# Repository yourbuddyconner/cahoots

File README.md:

# Cahoots

Cahoots is a private network that only exists between people who have met in person. Meeting takes five minutes in a room: your devices make a shared secret that nobody outside the room has seen. After that you can message, log in and tunnel to each other with keys that no server ever had, and the keys rotate from that secret for years.

## The mental model

A one-time pad is a file of random bytes that a group of people share. To encrypt a message, you XOR it with fresh pad bytes. To decrypt, you XOR it with the same bytes. Each byte is used once and then destroyed. If the pad is truly random and never reused, no amount of computing power can break the encryption. That includes quantum computers.

The hard part is getting the same random file to every member without anyone else seeing it. Cahoots does this in person, at a **ceremony**:

1. A group meets in a room. Each person holds a Cahoots badge or a phone.
2. Each device generates random bytes from its hardware random number generator.
3. The devices swap those bytes over a wired touch link, or by showing each other animated codes. Each contribution is encrypted to the other members before it leaves the device, so a camera or an antenna in the room learns nothing.
4. Every device XORs all contributions into one shared pad.
5. Every device signs the list of seats with a key it made for this group, so the group has a signed roster and every member a key to sign with later.
6. The members read six check words aloud to confirm every device holds the same pad.

The group is now a **circle**. The pad is a key budget. Spending 32 bytes seeds a session of any size in WireGuard, HPKE, or age. An attacker then has to break both the math and the pad. Spending one byte per byte encrypts a short message that nothing can break. The device records every spend in a ledger and erases the bytes, so no key is ever used twice.

Ciphertext travels over the **Numbers Station**, an append-only public feed. Anyone can read it. Only circle members can decrypt or forge an entry.

A circle can also give a seat to a hosted software member, such as an AI agent. That member's copy of the pad lives inside a [Turnkey Verifiable Cloud (TVC)](https://docs.turnkey.com/features/verifiable-cloud/overview) enclave, and a pinned policy decides each read and send. This integration is optional. Circles without a hosted seat have a simple guarantee: nobody who runs the feed can read the circle.

## A badge with the chip

On a V1 board with the NXP SE051 secure element, the chip makes and holds each circle's seat key, and the key never leaves it. With it, a badge can:

- Show a proof from the chip that the seat key lives in it (attestation).
- Sign SSH logins, git commits and files. A laptop program asks, the badge shows the user and host, the commit's author and subject, or the file's first line and size, and it signs when both buttons are pressed.
- Sign a contact card and share its circle's card seal key, so a circle can swap cards.
- Sign grants as CBOR Web Tokens.
- Give an agent a grant to sign git commits on a budget, so each commit needs no press. The chip counts the uses.

A badge also keeps several circles at once, with nothing linking them, whether or not it has the chip: up to 16 on the Pico 2, and 4 on the Nano ESP32, which has no chip.

All of this is built and tested against a software chip, and on 2026-10-29 a Pico 2 with the SE051 did it on the bench: a ceremony with its seat key made in the chip, then a file and a git commit signed by the chip and verified by `ssh-keygen` and `git`. Attestation against NXP's root still waits. See [the roadmap](docs/plan.md) (M4f) and the [host program](crates/host/README.md).

## Repository layout

Every Rust crate lives under `crates/`. The PWA lives under `web/app`.

| Path | Crate | What it holds | Status |
|---|---|---|---|
| `crates/core` | `cahoots-core` | The protocol: parameters, commit-then-reveal ceremony, XOR combine, check words, circle ID, message codec with one-time Poly1305, spent-range ledger, spend ordering, touch-link framing. `no_std` + `alloc`. | done (M1) |
| `crates/vectors` | `cahoots-vectors` | JSON test vectors generated from core. Every client must reproduce them. | done (M1) |
| `crates/objects` | `cahoots-objects` | The four objects a seat signs, as canonical CBOR in COSE_Sign1: grants, approvals, facts and receipts, each verified against the circle's signed manifest, with a JSON projection and vectors. `no_std`. | done (M1c) |
| `crates/custodian` | `cahoots-custodian` | The `Custodian` trait (`psk`, `spend`, `remaining`), the CBOR request and response messages, and `serve`, which answers a request only when the device consents. The `Chip` family (attest, sign for SSH, sign a card or a grant, release a seal key) is in [protocol](docs/protocol.md) section 6; a laptop program and a badge must come from the same release. `no_std`. | done (M4e) |
| `crates/chip` | `cahoots-chip` | The `ChipOps` trait a badge's key store speaks, a software chip for tests, and the SE051 backend (feature `se05x`) the Pico 2 uses. `no_std`. | done in software (M4f); the chip on the bench is not |
| `crates/provider` | `cahoots-provider` | The memory and encrypted-file custodians, the HKDF session-key derivation, and the old `PadProvider` name for `Custodian`. | done (S1) |
| `crates/hpke` | `cahoots-hpke` | HPKE `mode_psk` adapter (X25519 and X-Wing suites). | done (S1) |
| `crates/age-plugin-cahoots` | `age-plugin-cahoots` | age plugin: recipient `cahoots:<circle>`. | done (S1), untested against the `age` CLI |
| `crates/wireguard` | `cahoots-wireguard` | WireGuard `PresharedKey` helper and the `cahoots-wg` CLI: announce, peers, issue, accept over the feed or by paste; `--apply` runs `wg set`. | done (S1, N1); `scripts/wg-demo.sh` runs a two-host tunnel in CI |
| `crates/relay` | `cahoots-relay` | Numbers Station client shared by the CLIs. | done |
| `crates/wasm` | `cahoots-wasm` | Browser bindings: ceremony, circle, fountain-coded animated QR, QR rendering. | done (M2) |
| `web/app` | | Offline PWA phone and laptop client, including hello words for calls. | done (M2), camera scanning untested |
| `crates/phone` | `cahoots-phone` | The iOS app's state machine behind UniFFI: ceremonies as animated codes, circles as CBOR records, chat through the relay with an outbox, hello words. Swift supplies the enclave signer and HTTP. `scripts/ios-framework.sh` builds the XCFramework. | in progress (the Rust side; the app is not built yet) |
| `crates/hal` | `cahoots-hal` | HAL traits, the ceremony driver over any set of touch links (a pile, a ring, a pair), pile discovery (seat and count from the stack), SP 800-90B health tests, persistent ledger. `no_std`. | done (M4a) |
| `crates/badge` | `cahoots-badge` | The badge crate: the `Board` trait and the badge program that runs on it. It boots, runs the ceremony, keeps the circle, and shows the words, a key as a code, or serves custodian requests. `no_std`. | done (M4e) |
| `crates/host` | `cahoots-host` | Desktop simulator: socket Link, file PadStore, PNG Display. Four processes, each with a socket to both neighbours, run a ceremony. | done (M4a) |
| `crates/esp32s3` | `cahoots-esp32s3` | `esp-hal` firmware for the Arduino Nano ESP32 with the 1.54" e-paper and two buttons: the four HAL traits on real hardware, the pile over USB with the laptop as the other cards. Built with the esp toolchain, outside the workspace. | in progress (M4b, first board) |
| `crates/rp2350` | `cahoots-rp2350` | `rp235x-hal` firmware for the Raspberry Pi Pico 2 on V1's pin map: the e-paper, two buttons, the chip's TRNG, the pad and ledger in flash through the boot ROM, USB to a laptop and two UARTs up and down a pile. | done on a breadboard Pico 2 (M4b, 2026-10-27): a ceremony with the laptop as the pile, the circle kept in flash |
| `crates/dabao` | | Xous app for the Baochip-1x Dabao, the V2 card. | placeholder (M4c, M5) |
| `crates/chat` | `cahoots-chat` | End-to-end chat keyed by the circle root: epoch keys, sender ratchets, ChaCha20-Poly1305, plus the `cahoots-chat` CLI demo. | done (C1, C3) |
| `crates/station` | `cahoots-station` | The Numbers Station relay: hash-chained log, reuse refusal, long-poll feed, display page, per-client rate limit, log cap, Dockerfile, and the [deploy recipe](deploy/relay/README.md) for the default relay. | done (C2, C7; `relay.cahoots.network` is up); the [TVC](https://docs.turnkey.com/features/verifiable-cloud/overview) deploy pending |
| `crates/fuzz` | | `cargo-fuzz` targets for every parser. Not a workspace member. | done |
| `docs/` | | Protocol spec, threat model, use cases, plan, ceremony guide. | |

## Build and test

```sh
cargo test --workspace
cargo clippy --workspace --all-targets -- -D warnings
cargo build -p cahoots-core --no-default-features --target thumbv7em-none-eabi   # no_std check
cargo build -p cahoots-core --target wasm32-unknown-unknown
cargo run -p cahoots-vectors -- --check     # committed vectors are current
```

The pinned toolchain is in `rust-toolchain.toml`. CI runs these commands, with `--all-features` on clippy and test, and also builds `cahoots-hal` and `cahoots-chat` for `thumbv7em-none-eabi`.

## Security limits

- Confidentiality is information-theoretic only for circles labelled `TRNG`, and only while no pad byte is reused. `CSPRNG` circles are computationally secure.
- The circle tag proves that some member wrote a message, not which member.
- A stolen device exposes that device's pad.
- Erasure on phone storage is best effort.
- Circles that seat an agent trust the enclave with their pad.

See `docs/threat-model.md` for the full list.

## What it is for

`docs/tiers.md` defines the device tiers, from a phone (T0) to inspected silicon (T4), and the rule that a circle is only as protected as its least protected member. `docs/use-cases.md` lists concrete uses: group chat, and bootstrapping WireGuard and mesh networks from a ceremony. `docs/gatherings.md` is the concept of a card for every gathering: storage, messages from old circles, the web of trust a card accumulates, and a social network with no accounts. `docs/attested-data.md` surveys what a network of attested sensor readings, signed by the badge's key store chip, could be used for. `docs/diy-badge.md` is how to build a badge, in any of the three hardware families. `docs/plan.md` is the roadmap. `docs/glossary.md` defines the terms.

## Working rules

Correctness of the crypto is the product. Every spend path erases before output. Every tag compare is constant time. The message decoder is property-tested against arbitrary bytes. The code uses standards where they exist: Poly1305 (RFC 8439), BIP-39 words, HPKE (RFC 9180), and HKDF (RFC 5869).

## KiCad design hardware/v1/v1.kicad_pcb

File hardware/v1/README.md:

# V1: the first badge you can order

A 54 × 86 mm two-layer board that a Raspberry Pi Pico 2 solders onto. Front: the raw 1.54" e-paper (Good Display GDEY0154D67) on its 24-pin flex, two tactile switches, the pin half of a magnetic pogo connector at the top end with its pins up through the lid, two JST-SH sockets and a Qwiic socket at the bottom edge, and a three-turn NFC loop around the board's edge. Back: the Pico 2 crosswise with its USB at the right edge, a CR2032 holder, a power switch, the panel's boost circuit, the NXP SE051 secure element with a switch that opens its antenna, a 10-pin expansion socket, four pockets for 5 × 2 mm magnets.

The plan it belongs to is [docs/manufacturing.md](../../docs/manufacturing.md). The hand-built version that comes first, a Pico 2 and the Waveshare module on a proto board, uses the same pin map; the table is at the bottom.

## Status

Drawn, checked and quoted (2026-10-27, with the secure element and the loop): five boards, through ProvenMetal at JLCPCB, about to be ordered and not yet received. The schematic passes KiCad's electrical check, the board passes its design rule check, the three agree on every net (`check.py`), and every part in `bom.csv` is in JLCPCB's stock under the code written next to it (checked 2026-10-27 through ProvenMetal). What has not happened: a person looking at the 3D view and a 1:1 printout, and the flex connector's contact side confirmed against the panel's flex. See the review list.

## Files

| File | What |
|---|---|
| `design.py` | The single source: every part, pad, net and position, the Pico pin map, the panel pinout. |
| `make_sch.py` | Draws `v1.kicad_sch` from it: each part with a labelled stub on every pin. Plain python3. |
| `make_pcb.py` | Builds `v1.kicad_pcb`: footprints placed from the table, outline, slot, pours, edge keep-outs. KiCad's Python. |
| `route.py` | Exports the board for Freerouting and imports the result, then fills the pours. KiCad's Python. |
| `check.py` | Schematic netlist versus `design.py` versus the board. KiCad's Python. |
| `make_bom.py` | `bom.csv` in the assembler's columns. |
| `make.sh`, `hero.sh` | The whole pipeline; the angled two-sided render. |
| `v1.kicad_pro`, `v1.kicad_sch`, `v1.kicad_pcb`, `bom.csv` | The generated project. Open `v1.kicad_pro` in KiCad to look. |
| `schematic.png`, `front.png`, `back.png`, `hero.png` | Renders of the schematic, both sides of the board, and an angled view of both for an article. |
| `models/panel.wrl` | A box model of the panel, so the 3D view shows the glass and the flex. |
| `case.py`, `case/` | The tray and lid: STEP, STL for the printer, transparent WRL for the render. |
| `explode.py`, `assembly.png` | The parts sheet: the badge exploded into lid, panel, board, cell, pins and tray beside the assembled badge, with a numbered list. |
| `parts.py`, `parts.png` | Each piece alone, front and back: lid, panel, board, tray. |
| `models/` | Models for the parts the libraries lack: panel, magnets, cell, the two pogo halves. |

Regenerate everything:

```sh
cd hardware/v1
PY=/Applications/KiCad.app/Contents/Frameworks/Python.framework/Versions/Current/bin/python3
python3 make_sch.py && python3 make_bom.py
$PY make_pcb.py && $PY route.py export
java -jar freerouting.jar -de v1.dsn -do v1.ses -mp 400 -da        # Freerouting 2.5 on Java 25; 2.1 never finished this board, and 2.5 needs the passes
$PY route.py import && $PY check.py
kicad-cli pcb drc --severity-error v1.kicad_pcb
kicad-cli pcb render --side top -o front.png v1.kicad_pcb
kicad-cli sch export svg -o out v1.kicad_sch          # schematic.png is a rendering of that SVG
```

Edit `design.py`, never the generated files: the next run overwrites them.

## What is on it

**Pico 2.** Soldered flat through its castellations, components facing out, USB overhanging the right edge, BOOTSEL reachable. Flashing is drag-and-drop over that USB. The library footprint is the Pico 1's; the Pico 2 has no castellated debug pads, so those three are dropped.

**Panel.** The flex leaves the panel's bottom edge 8.5 mm from its left corner and runs straight down into the connector on the front. The boost circuit is the panel specification's reference circuit, page 28: 47 µH, a MOSFET switched by the panel's own GDR pin, one Schottky up to VGH, a capacitor and two Schottkys pumping VGL negative, a 2.2 Ω sense resistor, and a 1 µF on each driven rail. BS1 to ground selects 4-wire SPI. The MOSFET is the AO3400A rather than the reference's Si1308EDL because it is a stocked basic part; its 30 V rating clears the panel's gate voltages.

**Rules.** Tracks are 0.25 mm with 0.2 mm clearance everywhere the router draws them. The board's minimums are JLCPCB's floor, 0.127 mm for both, which only the SE051's escape stubs use: its pads are on a 0.4 mm pitch, and each used pad gets a short locked stub at that width before the router takes over.

**Power.** CR2032 into a slide switch, through a Schottky into the Pico's VSYS. The Pico's buck-boost makes 3.3 V from anything above 1.8 V. The diode keeps USB power out of the cell. Whether a coin cell survives a ceremony is the open measurement in the manufacturing plan; the holder is the easy part to swap.

**Buttons.** A is next, B is confirm, each to ground on the chip's pull-ups.

**Secure element.** U2 on the back at the top right is the NXP SE051C2 in its 3 × 3 mm HX2QFN20, on I2C0 beside the Qwiic socket, with 3.3 kΩ pull-ups on the bus (a Qwiic board adds its own in parallel, which is fine at 3.3 V). Its ENA pin is on GP2 through a 100 kΩ pull-up: the chip is on until the firmware pulls the pin low for deep power-down. VOUT is tied to VCC on the board, as the data sheet asks when ENA is used, so the chip's own rail (SE_VCC) has its own 100 nF. RST_N is tied high; the ISO 7816 pins are left open; the centre pad is grounded.

**Antenna.** ANT1 is a rectangular spiral on the front around the whole board, just inside the magnet pockets: three turns of 0.4 mm copper on a 0.8 mm pitch, 52 × 71 mm outside, its two ends at the top-right corner over the chip. It is drawn as copper lines inside the ANT1 footprint, a net tie between its two pads, so the board's rules understand that one piece of copper joins the switch's net to the chip's. The SE051 resonates its antenna with 56 pF, which asks for about 2.5 µH at 13.56 MHz; the loop is about 1.4 µH in free space (`design.py` prints the estimate), and C15, 39 pF across LA and LB at the chip, brings it to 13.6 MHz, with C16's footprint (27 pF) left empty for trimming. The Pico, the cell and the back pour sit inside the loop and will pull the inductance down, so expect the first measurement to land high and need C16. SW4, the same slide switch as the power switch, is in the LA line between the chip and the loop: open, the loop is not a closed conductor and the chip sees only C15. The ground pours stay 1.2 mm clear of the turns on both layers, the front has no pour inside the loop, and no tracks or vias cross the turns on the front, which is why the three sockets at the bottom edge, the only parts outside the loop, each get a via of their own above their contacts. The firmware keeps the contactless interface disabled regardless of the switch; both off is the shipped state. (A loop around the panel alone was drawn first; its bottom edge ran along the Pico's lower pad row and the router could not get the top half of the board out.)

**Peripherals.** J5 at the bottom centre of the front is a Qwiic (STEMMA QT) socket, the same JST-SH 4-pin part as the pile ports, in the Qwiic pin order: 1 GND, 2 3V3, 3 SDA, 4 SCL, on the Pico's I2C0 (GP8 and GP9). Any Qwiic board plugs in with its own cable. J6 on the back, under the Qwiic socket at the bottom edge, is a 10-pin JST-SH socket, the same low side-entry family as the three front sockets: 3V3, GND and eight of the Pico's spare GPIO, for whatever a firmware fork needs to drive, on a cable out of the bottom end. Nothing else on the board uses those pins. (It was a 2x5 pin header until 2026-10-28; the badge is meant to stay low, and a header is 8 mm tall.)

**Pile links.** Badges stack face to face. J4 at the top end of the front is the pin half of an Adafruit 5413 magnetic connector (Weilichuang MG005): five pogo pins on 2.54 mm, a magnet at each end, 2 A rated, 0.9 mm stroke, standing on the board with its pins up through a window in the lid, 1.2 mm proud of the top. The pad half is not on the board: it sits face down in a window in the tray floor, flush with the outside, and a short JST-SH pigtail wires it to the DN socket J3 (its pin 1 to J3 pin 1, pin 2 to J3 pin 3, pin 4 to J3 pin 4). Stack two badges and the lower one's pins meet the upper one's pads, pin for pin, the magnets holding them; pins 1 and 5 are ground, 2 and 4 the UART, 3 spare. Pin 3 carries no power: feeding one badge's regulator from another's is a question for V2, and two UART lines and ground are the pile. J2 and J3 are JST-SH 4-pin sockets at the bottom edge, UP and DN, for a cable to a badge on the bench or a laptop; a straight cable works because TX and RX are crossed between the two. There is no detect wire: a connected peer's TX holds our RX high, and the firmware keeps a pull-down on each RX. UP is UART0, DN is UART1.

## Pin map

| Signal | Pico 2 GPIO | Pico pin | Hand build: Waveshare module / part |
|---|---|---|---|
| EPD_SCK | GP18 | 24 | CLK |
| EPD_MOSI | GP19 | 25 | DIN |
| EPD_CS | GP17 | 22 | CS |
| EPD_DC | GP16 | 21 | DC |
| EPD_RST | GP20 | 26 | RST |
| EPD_BUSY | GP21 | 27 | BUSY |
| BTN_A | GP14 | 19 | switch A to GND |
| BTN_B | GP15 | 20 | switch B to GND |
| I2C_SDA | GP8 | 11 | J5 pin 3 (Qwiic SDA), U2 pin 9 |
| I2C_SCL | GP9 | 12 | J5 pin 4 (Qwiic SCL), U2 pin 10 |
| SE_ENA | GP2 | 4 | U2 pin 11; low is deep power-down, 100 kΩ pull-up |
| GP6, GP7 | GP6, GP7 | 9, 10 | J6 pins 3, 4 (J6 pin 1 is 3V3, pin 2 GND) |
| GP10, GP11, GP12, GP13 | GP10 to GP13 | 14, 15, 16, 17 | J6 pins 5, 6, 7, 8 |
| GP22, GP26 | GP22, GP26 | 29, 31 | J6 pins 9, 10 |
| UP_TX | GP0 | 1 | J4 pin 2, J2 pin 3 |
| UP_RX | GP1 | 2 | J4 pin 4, J2 pin 4; pull-down, high means a peer |
| DN_RX | GP5 | 7 | J3 pin 3, and through the pigtail the floor pad 2; pull-down, high means a peer |
| DN_TX | GP4 | 6 | J3 pin 4, floor pad 4 |
| 3V3 | 3V3 | 36 | module VCC |
| GND | GND | 3, 8, 13, 18, 23, 28, 38 | module GND, switches, pogo pins 1 and 5, both sockets' pin 1 |
| VSYS | VSYS | 39 | CR2032 + through the switch and a Schottky |

The Pico 2 firmware must use this table. For the hand build the Waveshare module replaces the panel, the connector and the whole boost circuit, since it carries them on its own board.

## The case

Two printed parts that click together, drawn by `case.py` from the same table (`CASE` in `design.py`), in `case/`: `tray.step`/`.stl` and `lid.step`/`.stl`, plus `.wrl` copies KiCad shows in the 3D view, transparent like the acrylic version will be.

- **Tray.** The board drops in face up onto a ledge. The floor sits 5.6 mm under the board, past the Pico and the cell in its holder, with a notch for the USB socket, three openings in the end wall for the cables (the middle one continues below the board for the expansion socket on the back), two openings in the floor under the slide switches, the pad half's window, four magnet pockets.
- **Lid.** A 2 mm plate on a 4 mm skirt that wraps outside the tray's wall. The panel is taped to the board, not to the lid, so the board comes out of the case as one unit with its screen (decided 2026-10-28; the first drawing glued the panel into the lid for a flush top). The plate's window shows the active area with a 1.5 mm lip over the panel's edge, and a frame under the lip comes down to 0.15 mm above the glass so the panel cannot lift, with a gap where the flex leaves; the glass sits about 3 mm below the lid's top. Two 7 mm holes over the switch stems, the pogo window, three socket windows, four magnet pockets, and the cable openings continued through its skirt, which reaches down past the board to the snaps. Four ribs press the board onto the tray's ledge.
- **The click.** Four wedge bumps on the inside of the skirt, on short slit tabs so they flex, drop into four windows through the tray's wall. PETG flexes better than PLA for this; if a tab cracks, make `snap` smaller or `skirt_t` thinner in the table. Screws are the fallback and need no redesign: the corner pockets become holes.
- **Printing.** Tray floor down, lid plate down, no supports needed except the USB notch bridge. Clear PETG shows the board; resin or cut acrylic later from the same STEP.
- **Sizes.** Tray 57.8 × 89.8 mm; the badge in its case 60.4 × 92.4 × 15 mm.

The lid's cavity is 2.2 mm high, enough for the flex connector and the taped panel (1.15); the pogo body (4.0) and the socket bodies (4.3) rise into windows in the 2 mm plate, and the pad half sits in a matching window in the floor. The badge is 13.4 mm thick.

Regenerate: `python3 case.py` with CadQuery installed (`python3 -m venv cq && cq/bin/pip install cadquery && cq/bin/python case.py`), then `make.sh` picks the models up.

## Review before ordering

1. **Flex connector contact side.** The footprint is a bottom-contact, flip-lock 0.5 mm connector. The panel's flex must present its contacts on the matching side when it runs straight down from the panel. If the flex's contacts face the other way, swap to a top-contact part of the same footprint family, or fold the flex. This is the classic mistake with e-paper; check it against a real panel in hand.
2. **Connector orientation.** Pin 1 of the connector must meet pin 1 of the flex, which is the panel's left pin in its drawing. Confirm in the 3D view with the flex overlaid.
3. **Part numbers.** Done 2026-10-27: every line in `bom.csv` resolves to a part in JLCPCB's stock (the 2.2 Ω sense resistor had the code of a 22 Ω part; fixed). The Pico 2 and the pogo pins are marked not fitted and soldered by hand; so is C16, the antenna trim.
4. **Battery holder footprint.** Drawn as MYOUNG BS-07; if the stocked holder is another family, the footprint changes.
5. **Pogo pair.** The footprint is drawn from the Weilichuang drawing, not a library part: check the 1.0 mm drills on 2.54 mm and the 4.0 mm body height against a real one before ordering boards. Print a tray and lid and stack two: the pins should land on the pads with the magnets pulling.
6. **Thickness and the tray.** Panel 1 mm plus the connector's 2 mm on the front; Pico 1 mm plus its parts and the holder on the back. The tray design is not here yet.
7. **Look at it.** Open `v1.kicad_pro`, press Alt-3 for the 3D view, and print the front at 1:1.
8. **The antenna.** When boards arrive: with SW4 closed and the chip's contactless interface enabled, read the chip with an NFC reader and note the distance. If it reads only when touching or not at all, measure the loop's resonance (a nanoVNA across LA and LB with the chip out of circuit, or by sweeping the reader) and fit C16 to pull it to 13.56 MHz. The loop geometry and the two capacitor footprints are in `design.py`; the exposed-pad size of the QFN-20 footprint is KiCad's generic 1.65 mm, not NXP's drawing, which only matters for the solder joint of a pad that is electrically unused.
9. **The switches.** SW1 and SW4 are on the back, facing the tray floor, which has a 9 × 5 mm opening under each (`switch_win` in the case table) for a fingernail. Check the openings land on the actuators with a printed tray before gluing anything.

## Not in V1

Flash encryption in firmware, the dock, the thin cell, the final tray. Those are V2's questions once the power measurement is in.

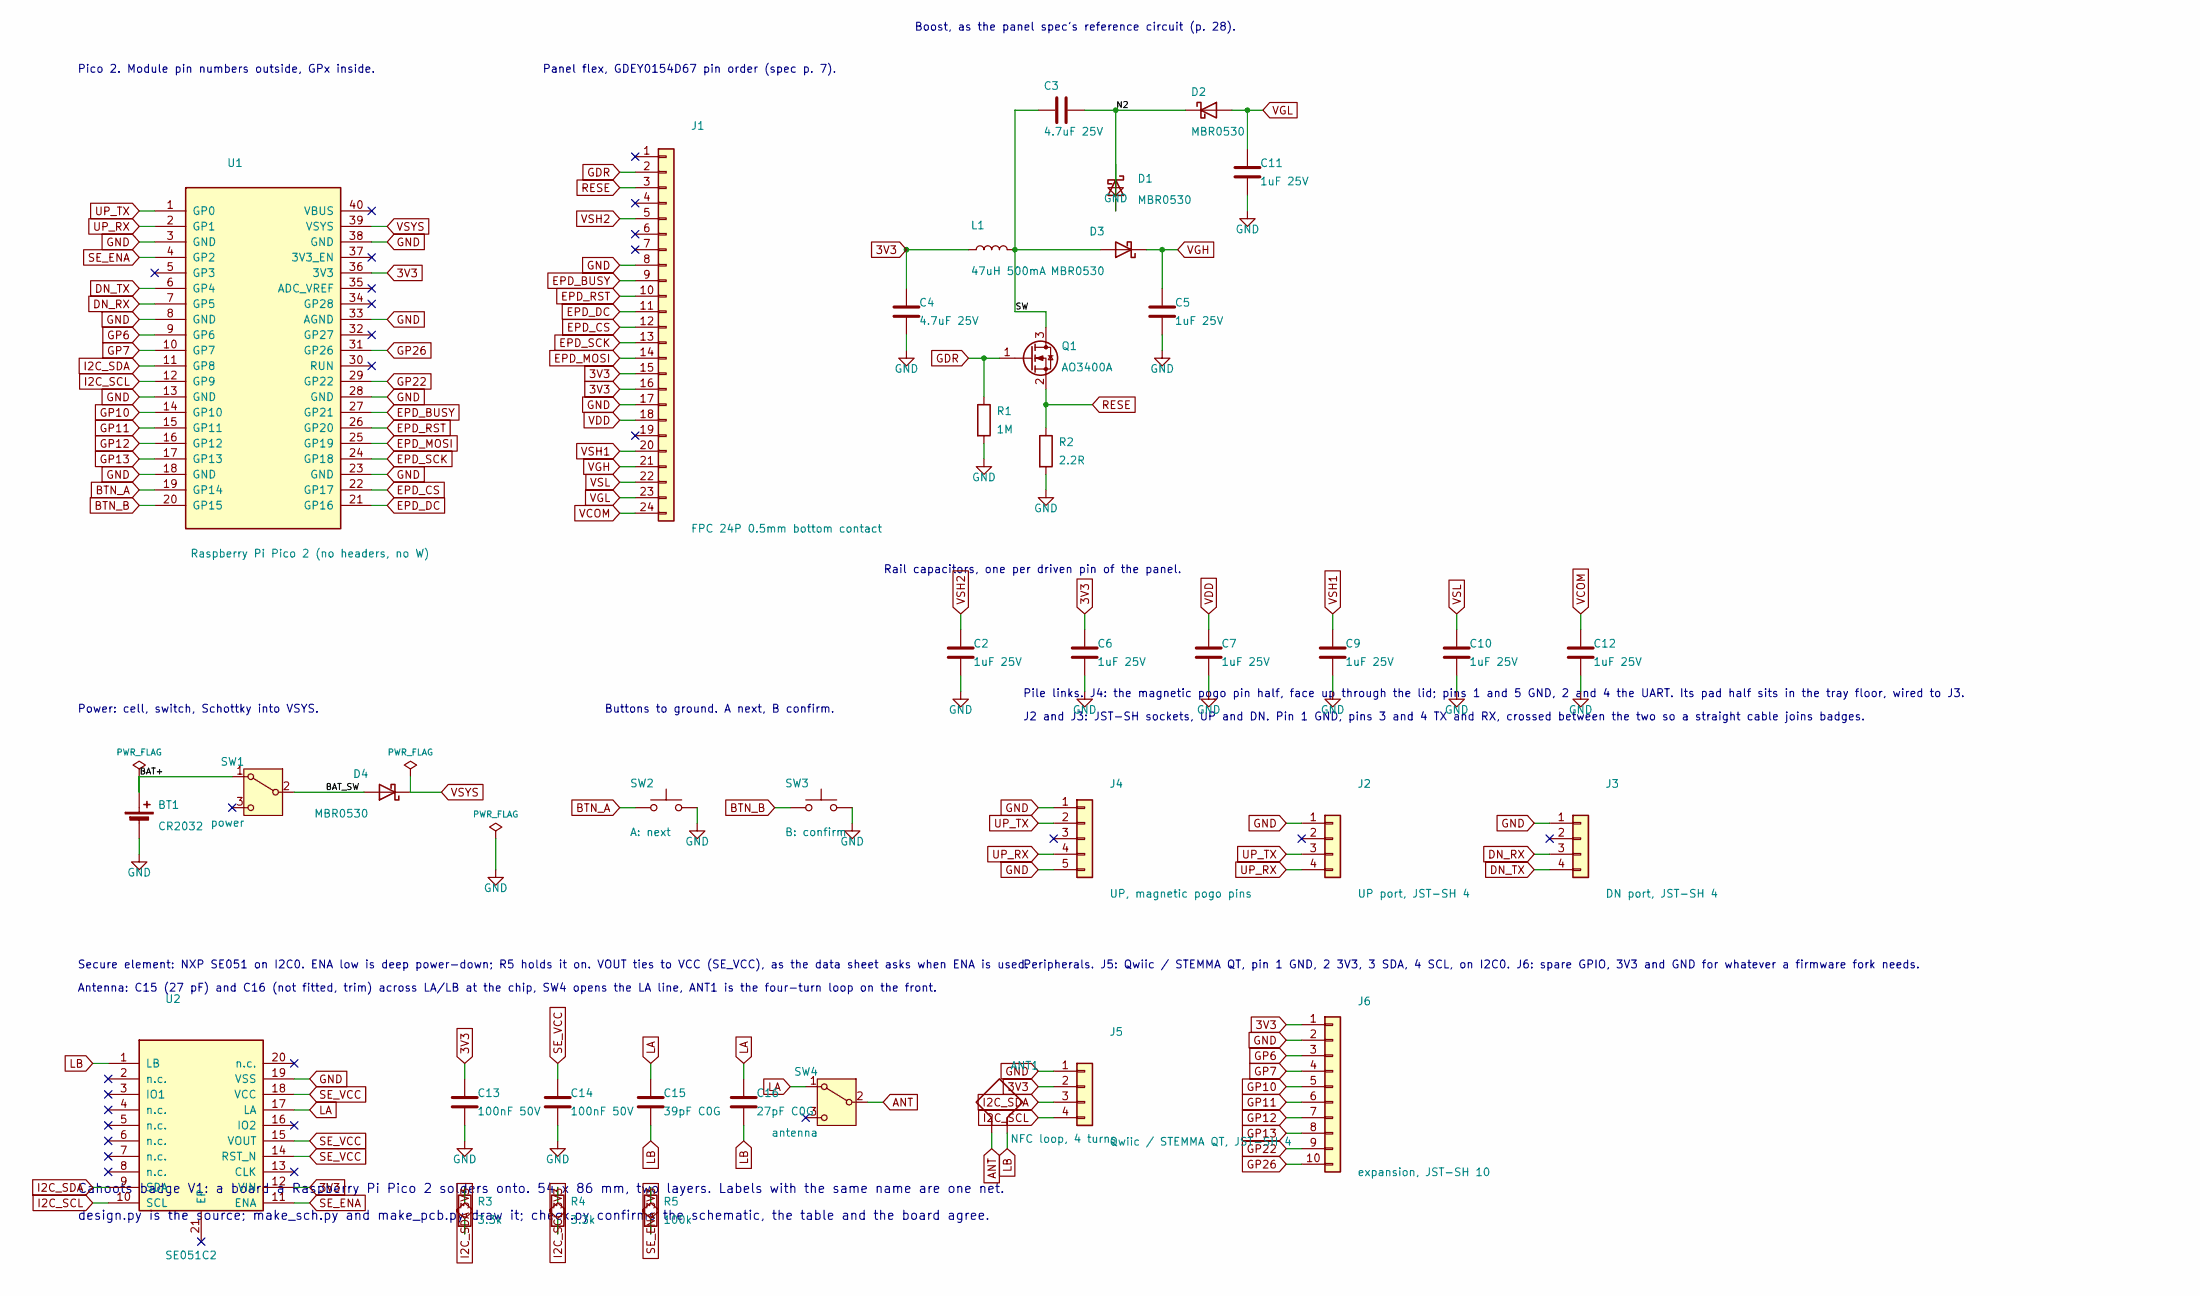
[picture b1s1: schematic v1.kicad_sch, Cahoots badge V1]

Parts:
ANT1: NFC loop, 4 turns; NFC_loop; LCSC board copper
BT1: CR2032; BatteryHolder_MYOUNG_BS-07-A1BJ001_CR2032; LCSC C2979167 MYOUNG BS-07-A1BJ001
C2, C5, C6, C7, C9, C10, C11, C12: 1uF 25V; C_0603_1608Metric; LCSC C15849
C3, C4: 4.7uF 25V; C_0805_2012Metric; LCSC C1779
C13, C14: 100nF 50V; C_0603_1608Metric; LCSC C14663
C15: 39pF C0G; C_0603_1608Metric; LCSC C107049 CC0603JRNPO9BN390, 39 pF
C16: 27pF C0G; C_0603_1608Metric; LCSC C107045 not fitted: antenna trim
D1, D2, D3, D4: MBR0530; D_SOD-123; LCSC C77336
J1: FPC 24P 0.5mm bottom contact; Hirose_FH12-24S-0.5SH_1x24-1MP_P0.50mm_Horizontal; LCSC C2856805 XUNPU FPC-05F-24PH20 (verify c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
J2: UP port, JST-SH 4; JST_SH_SM04B-SRSS-TB_1x04-1MP_P1.00mm_Horizontal; LCSC C160404 JST SM04B-SRSS-TB
J3: DN port, JST-SH 4; JST_SH_SM04B-SRSS-TB_1x04-1MP_P1.00mm_Horizontal; LCSC C160404 JST SM04B-SRSS-TB
J4: UP, magnetic pogo pins; Pogo_MG005_1x05; LCSC Adafruit 5413 pair, pin half
J5: Qwiic / STEMMA QT, JST-SH 4; JST_SH_SM04B-SRSS-TB_1x04-1MP_P1.00mm_Horizontal; LCSC C160404 JST SM04B-SRSS-TB
J6: expansion, JST-SH 10; JST_SH_SM10B-SRSS-TB_1x10-1MP_P1.00mm_Horizontal; LCSC C160409 JST SM10B-SRSS-TB
L1: 47uH 500mA; L_Changjiang_FNR4030S; LCSC C167888 FNR4030S470MT
Q1: AO3400A; SOT-23; LCSC C20917 (Si1308EDL in the reference; 30 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
R1: 1M; R_0603_1608Metric; LCSC C22935
R2: 2.2R; R_0603_1608Metric; LCSC C22939 0603WAF220KT5E, 2.2 ohm
R3, R4: 3.3k; R_0603_1608Metric; LCSC C22978
R5: 100k; R_0603_1608Metric; LCSC C25803
SW1: power; SW_SPDT_Shouhan_MSK12C02; LCSC C431540 MSK-12C02
SW2: A: next; SW_Push_1P1T_XKB_TS-1187A; LCSC C318884 TS-1187A-B-A-B
SW3: B: confirm; SW_Push_1P1T_XKB_TS-1187A; LCSC C318884 TS-1187A-B-A-B
SW4: antenna; SW_SPDT_Shouhan_MSK12C02; LCSC C431540 MSK-12C02
U1: Raspberry Pi Pico 2 (no headers, no W); RaspberryPi_Pico_SMD; LCSC not fitted: solder by hand
U2: SE051C2; QFN-20-1EP_3x3mm_P0.4mm_EP1.65x1.65mm; LCSC C5202100 NXP SE051C2HQ1/Z01XDZ

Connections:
3V3: C4.1, C6.1, C13.1, J1.15, J1.16, J5.2, J6.1, L1.1, R3.2, R4.2, R5.2, U1.36 (3V3), U2.12 (VIN)
ANT: ANT1.1, SW4.2 (B)
BAT+: BT1.1 (+), SW1.1 (A)
BAT_SW: D4.2 (A), SW1.2 (B)
BTN_A: SW2.1, U1.19 (GP14)
BTN_B: SW3.1, U1.20 (GP15)
DN_RX: J3.3, U1.7 (GP5)
DN_TX: J3.4, U1.6 (GP4)
EPD_BUSY: J1.9, U1.27 (GP21)
EPD_CS: J1.12, U1.22 (GP17)
EPD_DC: J1.11, U1.21 (GP16)
EPD_MOSI: J1.14, U1.25 (GP19)
EPD_RST: J1.10, U1.26 (GP20)
EPD_SCK: J1.13, U1.24 (GP18)
GDR: J1.2, Q1.1 (G), R1.1
GP6: J6.3, U1.9 (GP6)
GP7: J6.4, U1.10 (GP7)
GP10: J6.5, U1.14 (GP10)
GP11: J6.6, U1.15 (GP11)
GP12: J6.7, U1.16 (GP12)
GP13: J6.8, U1.17 (GP13)
GP22: J6.9, U1.29 (GP22)
GP26: J6.10, U1.31 (GP26)
I2C_SCL: J5.4, R4.1, U1.12 (GP9), U2.10 (SCL)
I2C_SDA: J5.3, R3.1, U1.11 (GP8), U2.9 (SDA)
LA: C15.1, C16.1, SW4.1 (A), U2.17 (LA)
LB: ANT1.2, C15.2, C16.2, U2.1 (LB)
RESE: J1.3, Q1.2 (S), R2.1
SE_ENA: R5.1, U1.4 (GP2), U2.11 (ENA)
SE_VCC: C14.1, U2.14 (RST_N), U2.15 (VOUT), U2.18 (VCC)
SW: C3.1, D3.2 (A), L1.2, Q1.3 (D)
UP_RX: J2.4, J4.4, U1.2 (GP1)
UP_TX: J2.3, J4.2, U1.1 (GP0)
VCOM: C12.1, J1.24
VDD: C7.1, J1.18
VGH: C5.1, D3.1 (K), J1.21
VGL: C11.1, D2.2 (A), J1.23
VSH1: C9.1, J1.20
VSH2: C2.1, J1.5
VSL: C10.1, J1.22
VSYS: D4.1 (K), U1.39 (VSYS)

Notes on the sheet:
Pico 2. Module pin numbers outside, GPx inside.
Panel flex, GDEY0154D67 pin order (spec p. 7).
Boost, as the panel spec's reference circuit (p. 28).
Rail capacitors, one per driven pin of the panel.
Power: cell, switch, Schottky into VSYS.
Buttons to ground. A next, B confirm.
Pile links. J4: the magnetic pogo pin half, face up through the lid; pins 1 and 5 GND, 2 and 4 the UART. Its pad half sits in the tray floor, wired to J3.
J2 and J3: JST-SH sockets, UP and DN. Pin 1 GND, pins 3 and 4 TX and RX, crossed between the two so a straight cable joins badges.
Peripherals. J5: Qwiic / STEMMA QT, pin 1 GND, 2 3V3, 3 SDA, 4 SCL, on I2C0. J6: spare GPIO, 3V3 and GND for whatever a firmware fork needs.
Secure element: NXP SE051 on I2C0. ENA low is deep power-down; R5 holds it on. VOUT ties to VCC (SE_VCC), as the data sheet asks when ENA is used.
Antenna: C15 (27 pF) and C16 (not fitted, trim) across LA/LB at the chip, SW4 opens the LA line, ANT1 is the four-turn loop on the front.
Cahoots badge V1: a board a Raspberry Pi Pico 2 solders onto. 54 x 86 mm, two layers. Labels with the same name are one net.
design.py is the source; make_sch.py and make_pcb.py draw it; check.py confirms the schematic, the table and the board agree.

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
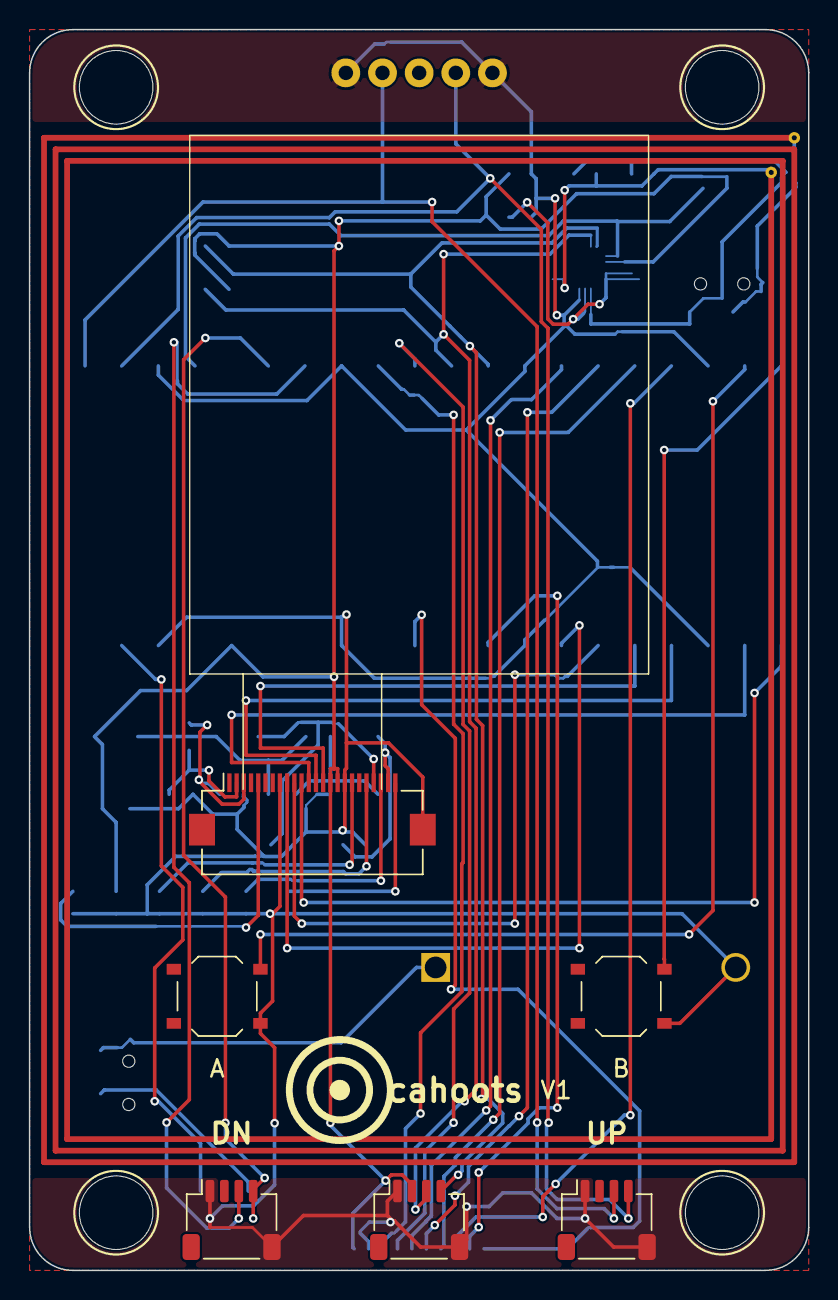
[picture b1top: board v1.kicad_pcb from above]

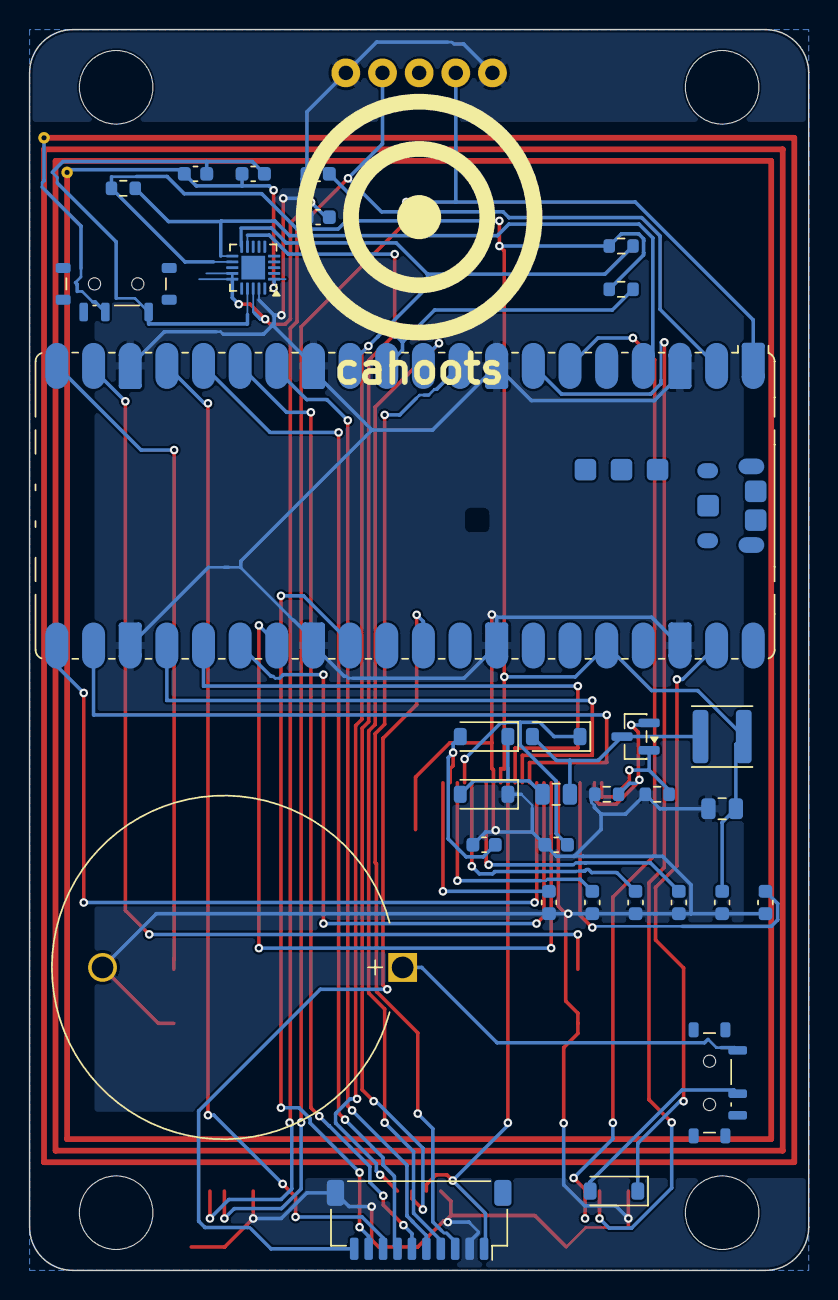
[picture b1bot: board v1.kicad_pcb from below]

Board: 2 copper layers, 54.0 x 86.0 mm, 46 parts (31 on the bottom side), 43 nets.

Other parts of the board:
CASE1: tray and lid; Case
DS1: GDEY0154D67; Panel_GDEY0154D67
M1, M2, M3, M4: 5x2 mm disc; Magnet_NPTH_D5.1mm
P1: DN, magnetic pads, in the tray floor; Pogo_MG005_tray

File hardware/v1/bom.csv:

Comment,Designator,Footprint,LCSC Part #,Note
CR2032,BT1,BatteryHolder_MYOUNG_BS-07-A1BJ001_CR2032,C2979167,MYOUNG BS-07-A1BJ001
100nF 50V,"C13,C14",C_0603_1608Metric,C14663,
39pF C0G,C15,C_0603_1608Metric,C107049,"CC0603JRNPO9BN390, 39 pF"
27pF C0G,C16,C_0603_1608Metric,C107045,not fitted: antenna trim
4.7uF 25V,"C3,C4",C_0805_2012Metric,C1779,
1uF 25V,"C10,C11,C12,C2,C5,C6,C7,C9",C_0603_1608Metric,C15849,
MBR0530,"D1,D2,D3,D4",D_SOD-123,C77336,
FPC 24P 0.5mm bottom contact,J1,Hirose_FH12-24S-0.5SH_1x24-1MP_P0.50mm_Horizontal,C2856805,XUNPU FPC-05F-24PH20 (verify contact side against the flex)
"UP port, JST-SH 4",J2,JST_SH_SM04B-SRSS-TB_1x04-1MP_P1.00mm_Horizontal,C160404,JST SM04B-SRSS-TB
"DN port, JST-SH 4",J3,JST_SH_SM04B-SRSS-TB_1x04-1MP_P1.00mm_Horizontal,C160404,JST SM04B-SRSS-TB
"UP, magnetic pogo pins",J4,Pogo_MG005_1x05,,"Adafruit 5413 pair, pin half"
"Qwiic / STEMMA QT, JST-SH 4",J5,JST_SH_SM04B-SRSS-TB_1x04-1MP_P1.00mm_Horizontal,C160404,JST SM04B-SRSS-TB
"expansion, JST-SH 10",J6,JST_SH_SM10B-SRSS-TB_1x10-1MP_P1.00mm_Horizontal,C160409,JST SM10B-SRSS-TB
47uH 500mA,L1,L_Changjiang_FNR4030S,C167888,FNR4030S470MT
AO3400A,Q1,SOT-23,C20917,"(Si1308EDL in the reference; 30 V, 5.7 A)"
1M,R1,R_0603_1608Metric,C22935,
2.2R,R2,R_0603_1608Metric,C22939,"0603WAF220KT5E, 2.2 ohm"
3.3k,"R3,R4",R_0603_1608Metric,C22978,
100k,R5,R_0603_1608Metric,C25803,
power,SW1,SW_SPDT_Shouhan_MSK12C02,C431540,MSK-12C02
A: next,SW2,SW_Push_1P1T_XKB_TS-1187A,C318884,TS-1187A-B-A-B
B: confirm,SW3,SW_Push_1P1T_XKB_TS-1187A,C318884,TS-1187A-B-A-B
antenna,SW4,SW_SPDT_Shouhan_MSK12C02,C431540,MSK-12C02
"Raspberry Pi Pico 2 (no headers, no W)",U1,RaspberryPi_Pico_SMD,,not fitted: solder by hand
SE051C2,U2,QFN-20-1EP_3x3mm_P0.4mm_EP1.65x1.65mm,C5202100,NXP SE051C2HQ1/Z01XDZ

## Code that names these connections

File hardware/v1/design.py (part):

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    "EPD_RST": "GP20", "EPD_BUSY": "GP21",
    "BTN_A": "GP14", "BTN_B": "GP15",
    "UP_TX": "GP0", "UP_RX": "GP1",     # UART0, the badge above. A peer is present while its TX holds our RX high.
    "DN_TX": "GP4", "DN_RX": "GP5",     # UART1, the badge below. Same rule: the RX pins carry pull-downs in firmware.
    "I2C_SDA": "GP8", "I2C_SCL": "GP9", # I2C0, the Qwiic socket J5 and the SE051.
    "SE_ENA": "GP2",                    # SE051 ENA: low puts the chip in deep power-down; a 100k pull-up keeps it on until the firmware says otherwise.
}
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for signal, gp in GPIO.items():
    pico_nets[str(pico_pin(gp))] = signal
pico_nets[str(pico_pin("3V3"))] = "3V3"
pico_nets[str(pico_pin("VSYS"))] = "VSYS"
for gp in HEADER:
    if gp.startswith("GP"):
        pico_nets[str(pico_pin(gp))] = gp
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
# ---- the magnetic pogo pair: the pin half on the board, the pad half loose in the tray floor ----
# Pins 1 and 5 ground, 2 and 4 the UART, 3 spare. Face to face, pin k meets pin k and the magnets
# attract. The pad half's pigtail: its pin 1 to J3 pin 1 (GND), pin 2 to J3 pin 3 (DN_RX), pin 4 to
# J3 pin 4 (DN_TX); so the lower badge's UP_TX on pin 2 reaches the upper badge's DN_RX.
part("J4", "Connector_Generic:Conn_01x05", "cahoots:Pogo_MG005_1x05", "UP, magnetic pogo pins", "Adafruit 5413 pair, pin half", "front", (0.0, POGO_Y + POGO["d"] / 2 - POGO["pin_to_back"]), 0, {"1": "GND", "2": "UP_TX", "4": "UP_RX", "5": "GND"})
part("P1", None, "cahoots:Pogo_MG005_tray", "DN, magnetic pads, in the tray floor", "Adafruit 5413 pair, pad half; JST-SH 4 pigtail to J3", "front", (0.0, POGO_Y + POGO["d"] / 2 - POGO["pin_to_back"]), 0, {})

# ---- the secure element: NXP SE051 on I2C0, on the back at the top right, above the Pico (which ends at y 21.6; the chip sits high enough that its escape stubs clear the Pico's pad row) and inside the loop ----
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        print(f"{net:10s} {' '.join(f'{r}.{p}' for r, p in pins)}")
    pins_in_use = list(GPIO.values()) + [n for n in HEADER if n.startswith("GP")]
    assert len(pins_in_use) == len(set(pins_in_use)), "a Pico pin is used twice"
    assert GPIO["I2C_SDA"] == "GP8" and GPIO["I2C_SCL"] == "GP9"
    assert PARTS["J5"]["pins"] == {"1": "GND", "2": "3V3", "3": "I2C_SDA", "4": "I2C_SCL", "MP": "GND"}
    assert [PARTS["J6"]["pins"][str(i)] for i in range(1, 11)] == HEADER and PARTS["J6"]["pins"]["MP"] == "GND"
    assert "3" not in PARTS["J4"]["pins"], "pogo pin 3 stays spare"
    L = antenna_inductance_uH() * 1e-6
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# escapes straight up through the same spot, so its vias go in the gaps beside the sockets instead.
# A key "NET@REF" routes one pad of a net that has several such pads.
PORT_VIA_Y = -39.4
for _ref, _pins in (("J2", {"3": "UP_TX", "4": "UP_RX", "1": "GND"}), ("J3", {"3": "DN_RX", "4": "DN_TX", "1": "GND"})):
    for _num, _net in _pins.items():
        MANUAL[f"{_net}@{_ref}"] = [("pad", _ref, _num), ("via", None, PORT_VIA_Y)]
# The antenna line from the chip to its switch: the router keeps missing it, so it is drawn. It starts
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
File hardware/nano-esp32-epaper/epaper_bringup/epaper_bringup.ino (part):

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#include "qrcode.h" // the board package's generator, not the QRCode library
#include "types.h"

#define EPD_CS 10
#define EPD_DC 9
#define EPD_RST 8
#define EPD_BUSY 7
#define BTN_A 2 // next
#define BTN_B 3 // confirm

// The words font, 12 px per letter. The left column is left-aligned and the right column right-aligned,
// so a row holds up to 15 letters plus a 4 px gap. The one pair that cannot fit, 8 + 8 letters, is 0.2%
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  uint32_t until = millis() + 3000;
  while (!Serial && millis() < until) delay(10); // runs unattended too
  Serial.println("cahoots screen bring-up: Nano ESP32 + Waveshare 1.54 V2, two buttons");
  pinMode(BTN_A, INPUT_PULLUP);
  pinMode(BTN_B, INPUT_PULLUP);
  delay(50);
  for (Btn* b : {&btnA, &btnB}) {
    b->down = digitalRead(b->pin) == LOW; // a held button is not a press
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
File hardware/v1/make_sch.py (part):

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
# Boost circuit, drawn as in the specification's reference circuit (p. 28), left to right:
# 3V3 -> L1 -> SW node -> D3 -> VGH, with Q1 switching SW to ground through the sense resistor,
# and C3/D1/D2 pumping VGL negative from the same SW node.
BX, BY = 175.26, 73.66
text("Boost, as the panel spec's reference circuit (p. 28).", BX - 12.7, BY - 35.56, 1.3)
l1 = place("L1", BX, BY, rot=90, ref_at=(-3.5, -4), val_at=(-3.5, 3.5))          # horizontal: pin 1 left, pin 2 right
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label("3V3", (in3[0] - G * 4, in3[1]), 180); wire((in3[0] - G * 4, in3[1]), in3)
c4 = place("C4", in3[0] - G * 4, BY + 10.16, ref_at=(2, -1.5), val_at=(2, 1.5))        # input cap to ground
wire((in3[0] - G * 4, in3[1]), c4["1"][0]); junction((in3[0] - G * 4, in3[1])); power("GND", c4["2"][0])
d3 = place("D3", sw[0] + 17.78, BY, rot=180, ref_at=(-3, -3), val_at=(-3, 3.5))      # anode at SW (right pin 2), cathode to VGH (left pin 1)
wire(sw, d3["2"][0]); junction(sw)
vgh = d3["1"][0]
route(vgh, (vgh[0] + G * 2, vgh[1])); label("VGH", (vgh[0] + G * 2, vgh[1]), 0)
c5 = place("C5", vgh[0] + G, BY + 10.16, ref_at=(2, -1.5), val_at=(2, 1.5))
wire((vgh[0] + G, vgh[1]), c5["1"][0]); junction((vgh[0] + G, vgh[1])); power("GND", c5["2"][0])
q1 = place("Q1", sw[0] + 2.54, BY + 17.78, ref_at=(5, -2), val_at=(5, 1.5))        # G left, D up, S down
d = q1["3"][0]
route(sw, (sw[0], d[1] - G), (d[0], d[1] - G), d); netname("SW", (sw[0], d[1] - G))
g = q1["1"][0]
route(g, (g[0] - G * 2, g[1])); label("GDR", (g[0] - G * 2, g[1]), 180)
r1 = place("R1", g[0] - G, g[1] + 10.16, ref_at=(2, -1.5), val_at=(2, 1.5))
wire((g[0] - G, g[1]), r1["1"][0]); junction((g[0] - G, g[1])); power("GND", r1["2"][0])
s = q1["2"][0]
r2 = place("R2", s[0], s[1] + 10.16, ref_at=(2, -1.5), val_at=(2, 1.5))
wire(s, r2["1"][0]); power("GND", r2["2"][0])
route((s[0], s[1] + G), (s[0] + G * 3, s[1] + G)); label("RESE", (s[0] + G * 3, s[1] + G), 0); junction((s[0], s[1] + G))
# negative pump off the same switch node
c3 = place("C3", sw[0] + 7.62, BY - 22.86, rot=90, ref_at=(-3, -4), val_at=(-3, 3.5))   # horizontal, pin 1 left at SW side
route(sw, (sw[0], c3["1"][0][1]), c3["1"][0])
n2 = c3["2"][0]
d1 = place("D1", n2[0] + 5.08, n2[1] + 12.7, rot=270, ref_at=(3.5, -1.5), val_at=(3.5, 2))  # cathode (pin 1) down to GND, anode (pin 2) up at N2
route(n2, (d1["2"][0][0], n2[1]), d1["2"][0]); junction((d1["2"][0][0], n2[1])); power("GND", d1["1"][0])
d2 = place("D2", n2[0] + 20.32, n2[1], rot=0, ref_at=(-3, -3), val_at=(-3, 3.5))          # cathode (pin 1) left at N2, anode (pin 2) right at VGL
route((d1["2"][0][0], n2[1]), d2["1"][0])
vgl = d2["2"][0]
route(vgl, (vgl[0] + G * 2, vgl[1])); label("VGL", (vgl[0] + G * 2, vgl[1]), 0)
c11 = place("C11", vgl[0] + G, vgl[1] + 10.16, ref_at=(2, -1.5), val_at=(2, 1.5))
wire((vgl[0] + G, vgl[1]), c11["1"][0]); junction((vgl[0] + G, vgl[1])); power("GND", c11["2"][0])
netname("N2", (d1["2"][0][0], n2[1]))
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sw1 = place("SW1", PX0 + 30.48, PY - 2.54, mirror="y", ref_at=(-3, -5), val_at=(-3, 5))
route(bt["1"][0], (bt["1"][0][0], sw1["1"][0][1]), sw1["1"][0]); netname("BAT+", (bt["1"][0][0], sw1["1"][0][1]))
no_connect(sw1["3"][0])
d4 = place("D4", PX0 + 50.8, sw1["2"][0][1], rot=180, ref_at=(-3, -3), val_at=(-3, 3.5))   # anode (pin 2) at the switch, cathode (pin 1) to VSYS
route(sw1["2"][0], d4["2"][0]); netname("BAT_SW", (sw1["2"][0][0] + G * 2, sw1["2"][0][1]))
route(d4["1"][0], (d4["1"][0][0] + G * 2, d4["1"][0][1])); label("VSYS", (d4["1"][0][0] + G * 2, d4["1"][0][1]), 0)
pwr_flag(bt["1"][0]); pwr_flag(d4["1"][0])
gnd_flag = (PX0 + 68.58, PY + 7.62); pwr_flag((gnd_flag[0], gnd_flag[1])); power("GND", gnd_flag)

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    route(a, (a[0], a[1] + G)); label(bottom, (a[0], a[1] + G), 90)
sw4 = place("SW4", SX + 124.46, SY + 7.62, mirror="y", ref_at=(-3, -5), val_at=(-3, 5))
route(sw4["1"][0], (sw4["1"][0][0] - G, sw4["1"][0][1])); label("LA", (sw4["1"][0][0] - G, sw4["1"][0][1]), 180)
route(sw4["2"][0], (sw4["2"][0][0] + G, sw4["2"][0][1])); label("ANT", (sw4["2"][0][0] + G, sw4["2"][0][1]), 0)
no_connect(sw4["3"][0])
labelled_block("ANT1", SX + 149.86, SY + 7.62, ref_at=(3, -6), val_at=(3, 6))

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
